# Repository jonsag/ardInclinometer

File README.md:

# ardInclinometer

An inclinometer built around MPU-6050 and ATmega MCUs  

Works on Arduino UNO, not working on barebone MCUs yet.

## Install latest avrdude from git repository

Install prerequisites  
>$ sudo apt install git build-essential cmake libelf-dev libusb-dev libusb-1.0-0-dev libhidapi-dev libftdi-dev libftdi1-dev flex bison  

Download repository  
>$ git clone [https://github.com/avrdudes/avrdude.git](https://github.com/avrdudes/avrdude.git)  

Build  
>$ cd avrdude  
>$ cmake -D CMAKE_BUILD_TYPE=Release -B build_linux  
>$ cmake --build build_linux  

Install (if you have ~/bin in your path)  
>$ cp -r build_linux/src ~/bin/avrdude-bin  
>$ ln -s avrdude-bin/avrdude ~/bin/avrdude  

Check version  
>$ avrdude -?  

    ...
    avrdude version 7.0-20220924 (8f478f0), URL: <https://github.com/avrdudes/avrdude>

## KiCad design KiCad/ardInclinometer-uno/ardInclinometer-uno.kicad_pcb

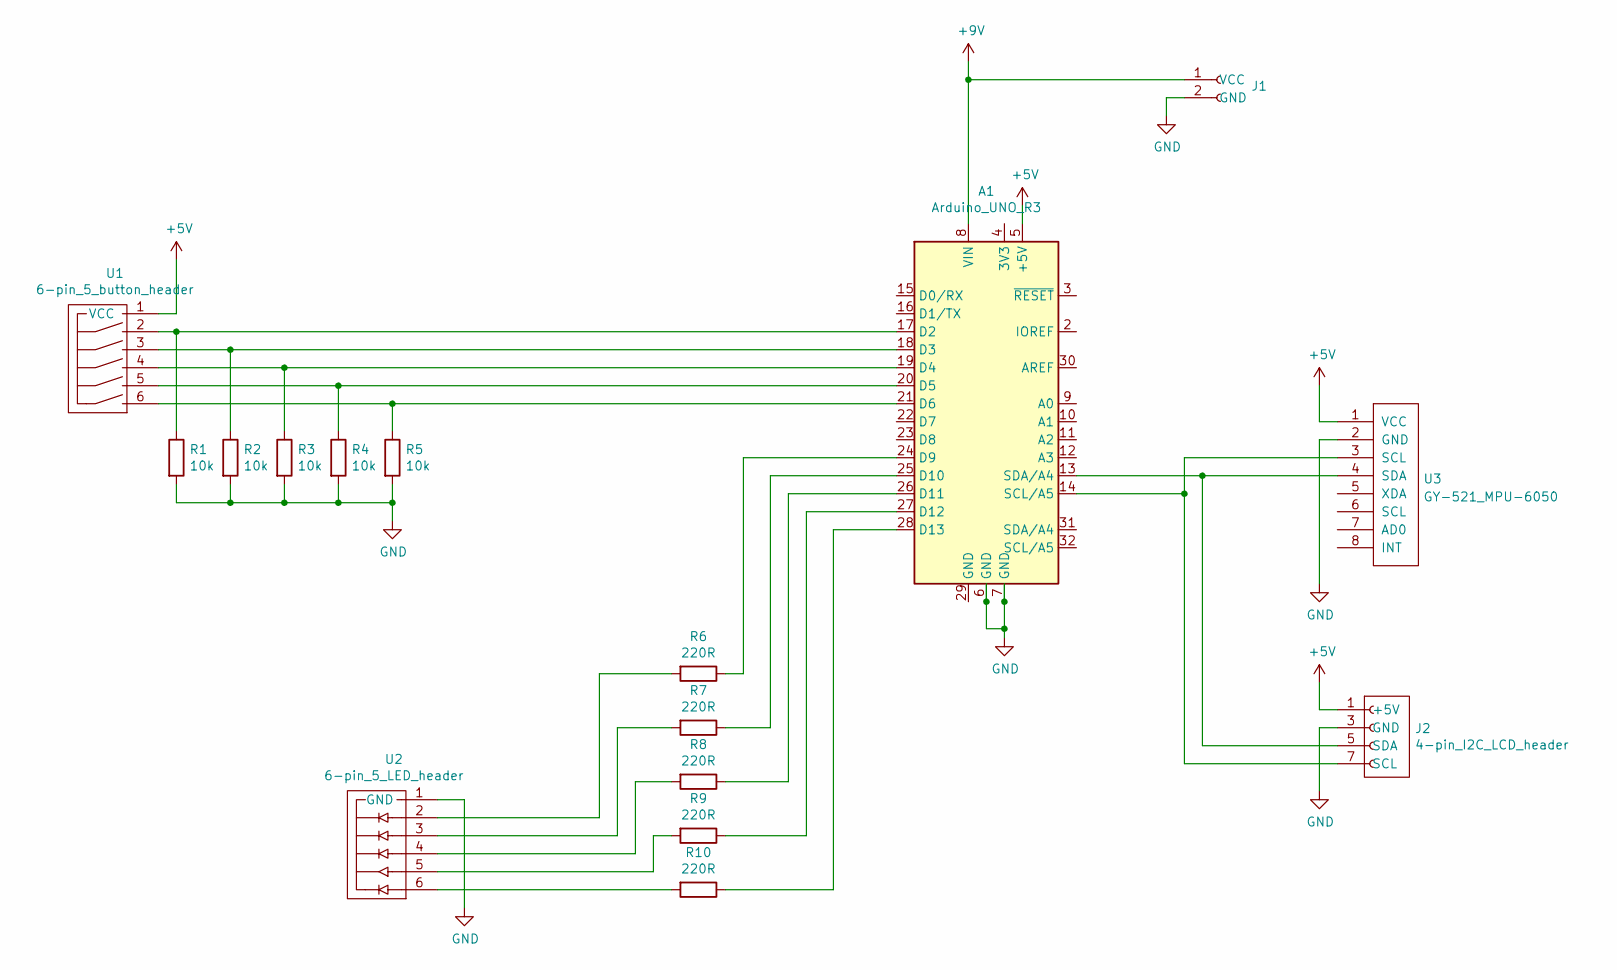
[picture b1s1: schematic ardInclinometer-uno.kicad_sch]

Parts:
A1: Arduino_UNO_R3; Arduino_UNO_R3_shield_large
J1: 2-pin_power_input_header; 2-pin_power_input_header_larger_pads
J2: 4-pin_I2C_LCD_header; 4-pin_I2C_LCD_header_larger
R1, R2, R3, R4, R5: 10k; R_Axial_DIN0207_L6.3mm_D2.5mm_P10.16mm_Horizontal_larger_pa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
R6, R7, R8, R9, R10: 220R; R_Axial_DIN0207_L6.3mm_D2.5mm_P10.16mm_Horizontal_larger_pa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
U1: 6-pin_5_button_header; 6-pin_5_switch_header_large
U2: 6-pin_5_LED_header; 6-pin_5_LED_header_large
U3: GY-521_MPU-6050

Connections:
+5V: A1.5 (+5V), J2.1 (+5V), U1.1 (VCC), U3.1 (VCC)
+9V: A1.8 (VIN), J1.1 (VCC)
GND: A1.6 (GND), A1.7 (GND), J1.2 (GND), J2.3 (GND), R1.2, R2.2, R3.2, R4.2, R5.2, U2.1 (GND), U3.2 (GND)
unnamed: A1.13 (SDA/A4), J2.5 (SDA), U3.4 (SDA)
unnamed: A1.14 (SCL/A5), J2.7 (SCL), U3.3 (SCL)
unnamed: A1.17 (D2), R1.1, U1.2
unnamed: A1.18 (D3), R2.1, U1.3
unnamed: A1.19 (D4), R3.1, U1.4
unnamed: A1.20 (D5), R4.1, U1.5
unnamed: A1.21 (D6), R5.1, U1.6
unnamed: A1.24 (D9), R6.1
unnamed: A1.25 (D10), R7.1
unnamed: A1.26 (D11), R8.1
unnamed: A1.27 (D12), R9.1
unnamed: A1.28 (D13), R10.1
unnamed: R6.2, U2.2
unnamed: R7.2, U2.3
unnamed: R8.2, U2.4
unnamed: R9.2, U2.5
unnamed: R10.2, U2.6

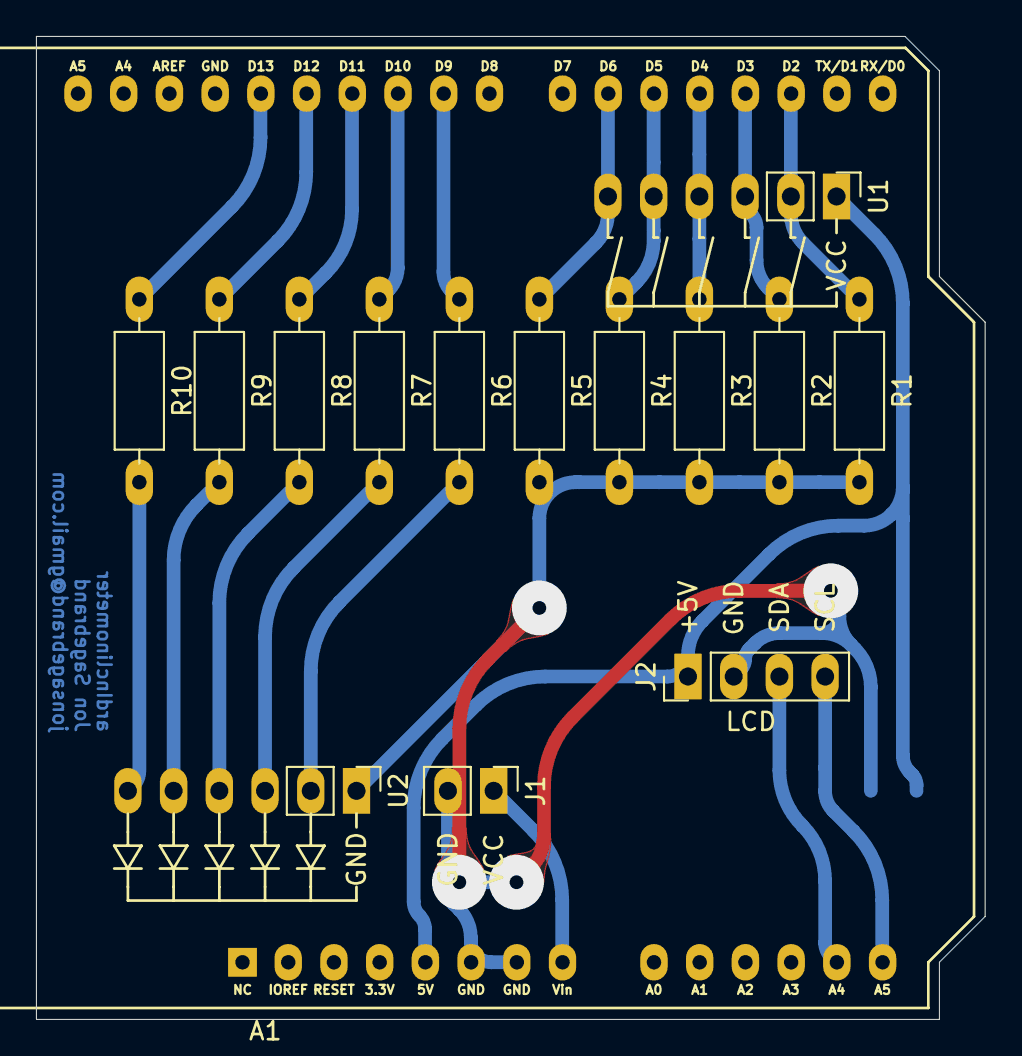
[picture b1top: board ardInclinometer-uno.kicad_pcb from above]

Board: 2 copper layers, 52.7 x 54.6 mm, 15 parts (0 on the bottom side), 20 nets.

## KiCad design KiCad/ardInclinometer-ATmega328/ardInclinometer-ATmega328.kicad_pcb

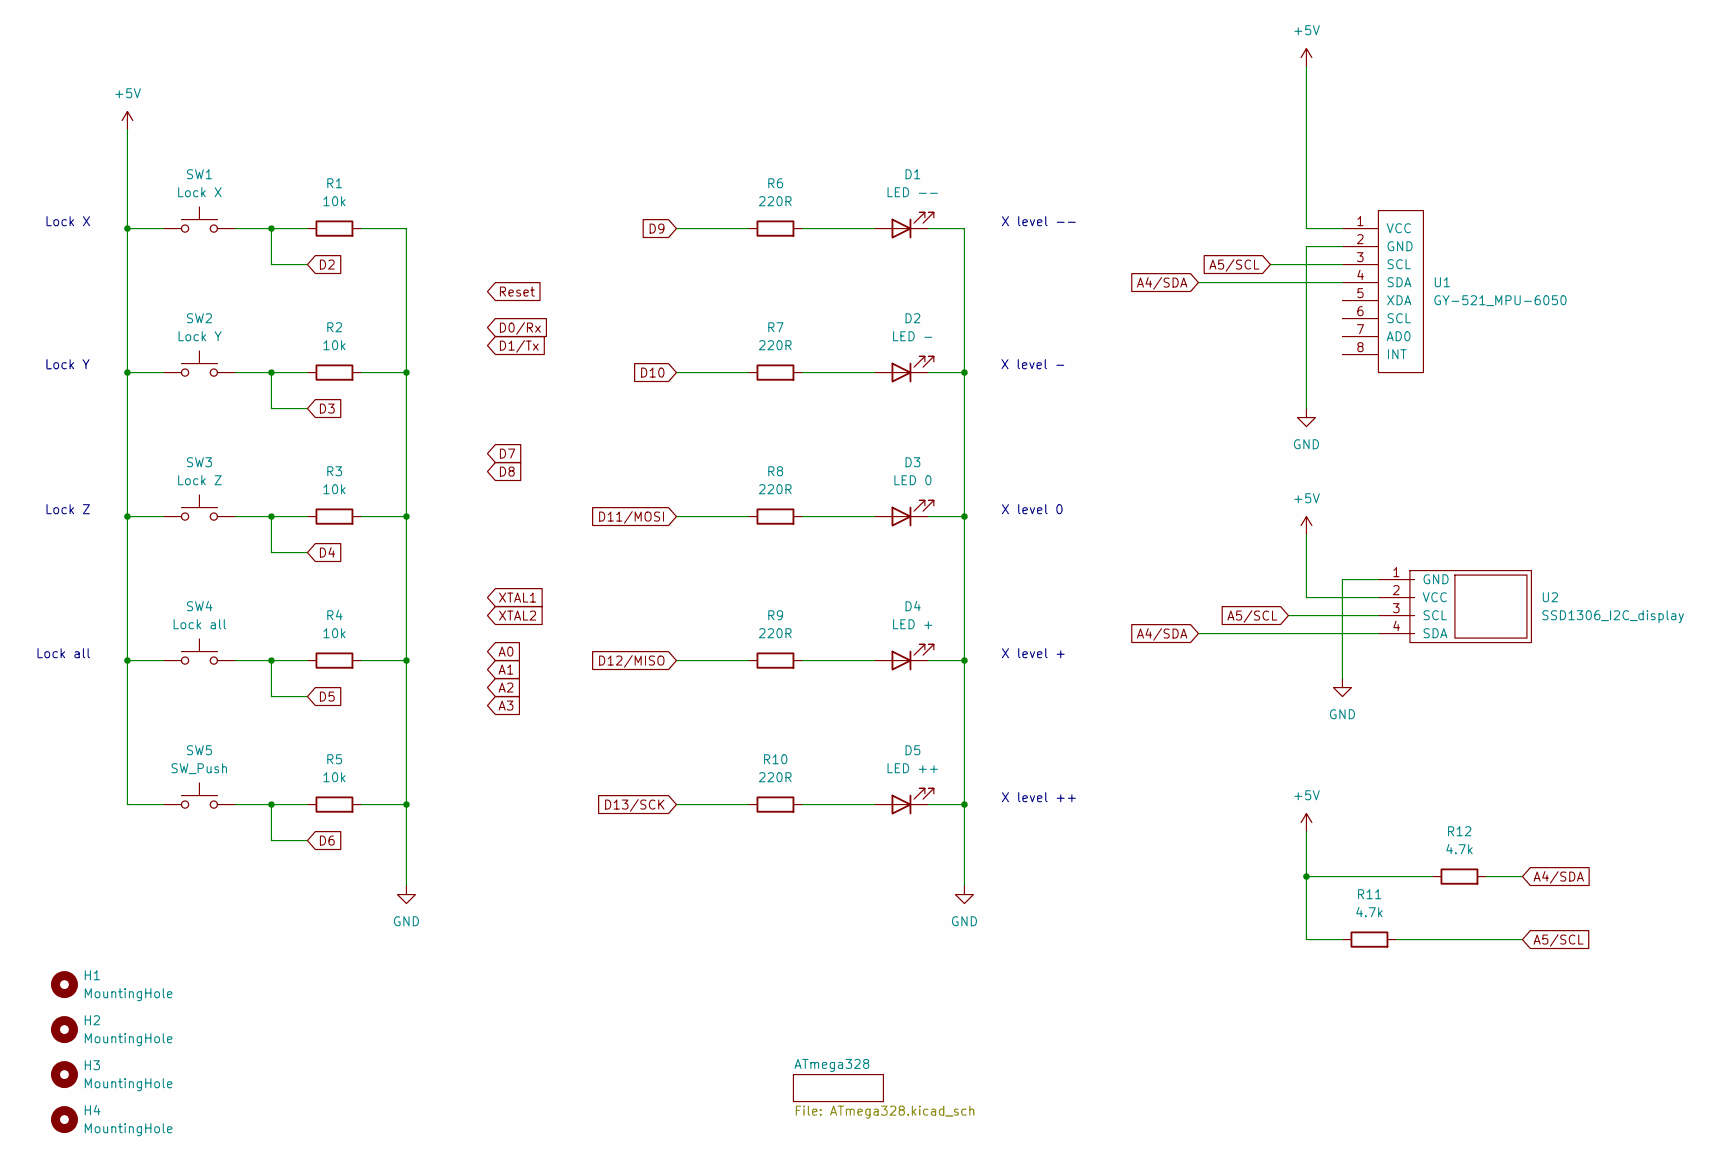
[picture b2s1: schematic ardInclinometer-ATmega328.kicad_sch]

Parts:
D1: LED --; LED_D5.0mm_large
D2: LED -; LED_D5.0mm_large
D3: LED 0; LED_D5.0mm_large
D4: LED +; LED_D5.0mm_large
D5: LED ++; LED_D5.0mm_large
H1, H2, H3, H4: MountingHole; MountingHole_3.2mm_M3
R1, R2, R3, R4, R5: 10k; R_Axial_DIN0207_L6.3mm_D2.5mm_P10.16mm_Horizontal_larger_pa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
R6, R7, R8, R9, R10: 220R; R_Axial_DIN0207_L6.3mm_D2.5mm_P10.16mm_Horizontal_larger_pa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
R11, R12: 4.7k; R_Axial_DIN0207_L6.3mm_D2.5mm_P10.16mm_Horizontal_large
SW1: Lock X; SW_PUSH_6mm_large
SW2: Lock Y; SW_PUSH_6mm_large
SW3: Lock Z; SW_PUSH_6mm_large
SW4: Lock all; SW_PUSH_6mm_large
SW5: SW_Push; SW_PUSH_6mm_large
U1: GY-521_MPU-6050; GY-521_MPU6050_w_header_large
U2: SSD1306_I2C_display; SSD1306_I2C_0.96_OLED_display_large

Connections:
+5V: R11.1, R12.1, SW1.1, SW2.1, SW3.1, SW4.1, SW5.1, U1.1 (VCC), U2.2 (VCC); also elsewhere on the board
A4/SDA: R12.2, U1.4 (SDA), U2.4 (SDA); also elsewhere on the board
A5/SCL: R11.2, U1.3 (SCL), U2.3 (SCL); also elsewhere on the board
D2: R1.1, SW1.2; also elsewhere on the board
D3: R2.1, SW2.2; also elsewhere on the board
D4: R3.1, SW3.2; also elsewhere on the board
D5: R4.1, SW4.2; also elsewhere on the board
D6: R5.1, SW5.2; also elsewhere on the board
D9: R6.1; also elsewhere on the board
D10: R7.1; also elsewhere on the board
D11/MOSI: R8.1; also elsewhere on the board
D12/MISO: R9.1; also elsewhere on the board
D13/SCK: R10.1; also elsewhere on the board
GND: D1.1 (K), D2.1 (K), D3.1 (K), D4.1 (K), D5.1 (K), R1.2, R2.2, R3.2, R4.2, R5.2, U1.2 (GND), U2.1 (GND); also elsewhere on the board
unnamed: D1.2 (A), R6.2
unnamed: D2.2 (A), R7.2
unnamed: D3.2 (A), R8.2
unnamed: D4.2 (A), R9.2
unnamed: D5.2 (A), R10.2

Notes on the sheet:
X level +
Lock all
Lock Z
X level -
X level ++
Lock X
Lock Y
X level --
X level 0

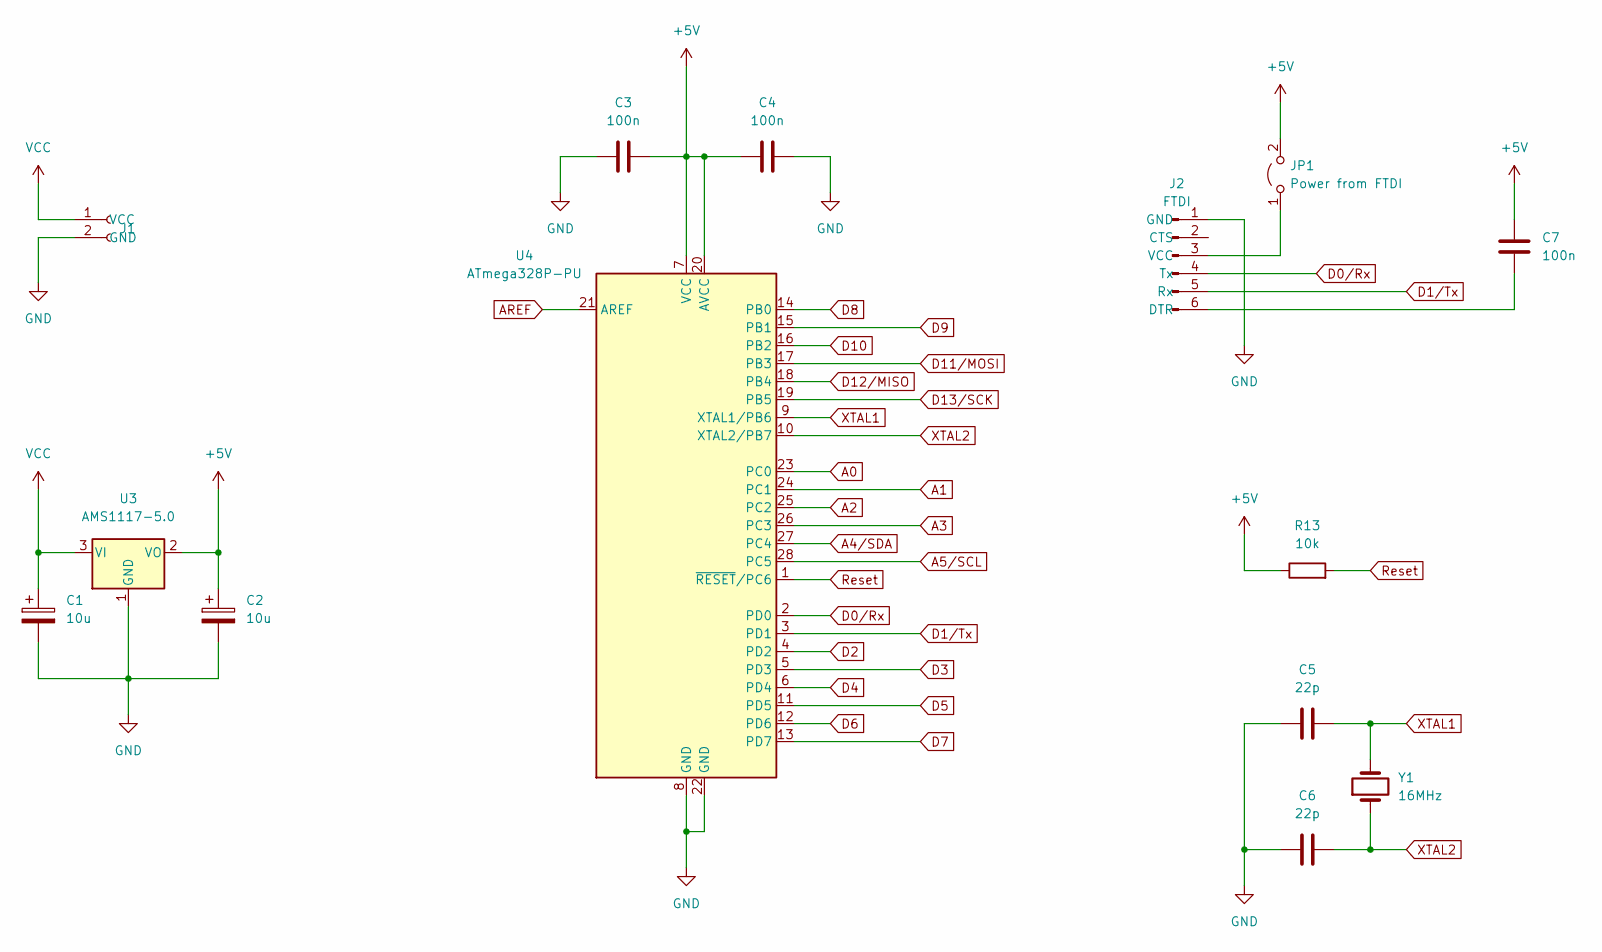
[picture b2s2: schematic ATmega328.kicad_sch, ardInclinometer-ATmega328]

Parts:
C1, C2: 10u; CP_Radial_D5.0mm_P2.00mm_larger
C3, C4, C7: 100n; C_Disc_D4.3mm_W1.9mm_P5.00mm_large
C5, C6: 22p; C_Disc_D3.0mm_W1.6mm_P2.50mm_larg
J1: Power in; 2-pin_power_input_header_larger_pads
J2: FTDI; 6-pin FTDI Programmer PinSocket large
JP1: Power from FTDI; Jumper_1x02_P2.54mm_large
R13: 10k; R_Axial_DIN0207_L6.3mm_D2.5mm_P10.16mm_Horizontal_larger_pa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
U3: AMS1117-5.0; SOT-223-3_TabPin2
U4: ATmega328P-PU; DIP-28_W7.62mm_LongPads w socket
Y1: 16MHz; Crystal_HC49-4H_Vertical_large

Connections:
+5V: C2.1, C3.1, C4.2, C7.2, JP1.2 (B), R13.1, U3.2 (VO), U4.7 (VCC), U4.20 (AVCC); also elsewhere on the board
A0: U4.23 (PC0)
A1: U4.24 (PC1)
A2: U4.25 (PC2)
A3: U4.26 (PC3)
A4/SDA: U4.27 (PC4); also elsewhere on the board
A5/SCL: U4.28 (PC5); also elsewhere on the board
AREF: U4.21 (AREF)
D0/Rx: J2.4 (Tx), U4.2 (PD0)
D1/Tx: J2.5 (Rx), U4.3 (PD1)
D2: U4.4 (PD2); also elsewhere on the board
D3: U4.5 (PD3); also elsewhere on the board
D4: U4.6 (PD4); also elsewhere on the board
D5: U4.11 (PD5); also elsewhere on the board
D6: U4.12 (PD6); also elsewhere on the board
D7: U4.13 (PD7)
D8: U4.14 (PB0)
D9: U4.15 (PB1); also elsewhere on the board
D10: U4.16 (PB2); also elsewhere on the board
D11/MOSI: U4.17 (PB3); also elsewhere on the board
D12/MISO: U4.18 (PB4); also elsewhere on the board
D13/SCK: U4.19 (PB5); also elsewhere on the board
GND: C1.2, C2.2, C3.2, C4.1, C5.1, C6.1, J1.2 (GND), J2.1 (GND), U3.1 (GND), U4.8 (GND), U4.22 (GND); also elsewhere on the board
unnamed: C7.1, J2.6 (DTR)
unnamed: J2.3 (VCC), JP1.1 (A)
Reset: R13.2, U4.1 (~RESET/PC6)
VCC: C1.1, J1.1 (VCC), U3.3 (VI)
XTAL1: C5.2, U4.9 (XTAL1/PB6), Y1.2
XTAL2: C6.2, U4.10 (XTAL2/PB7), Y1.1

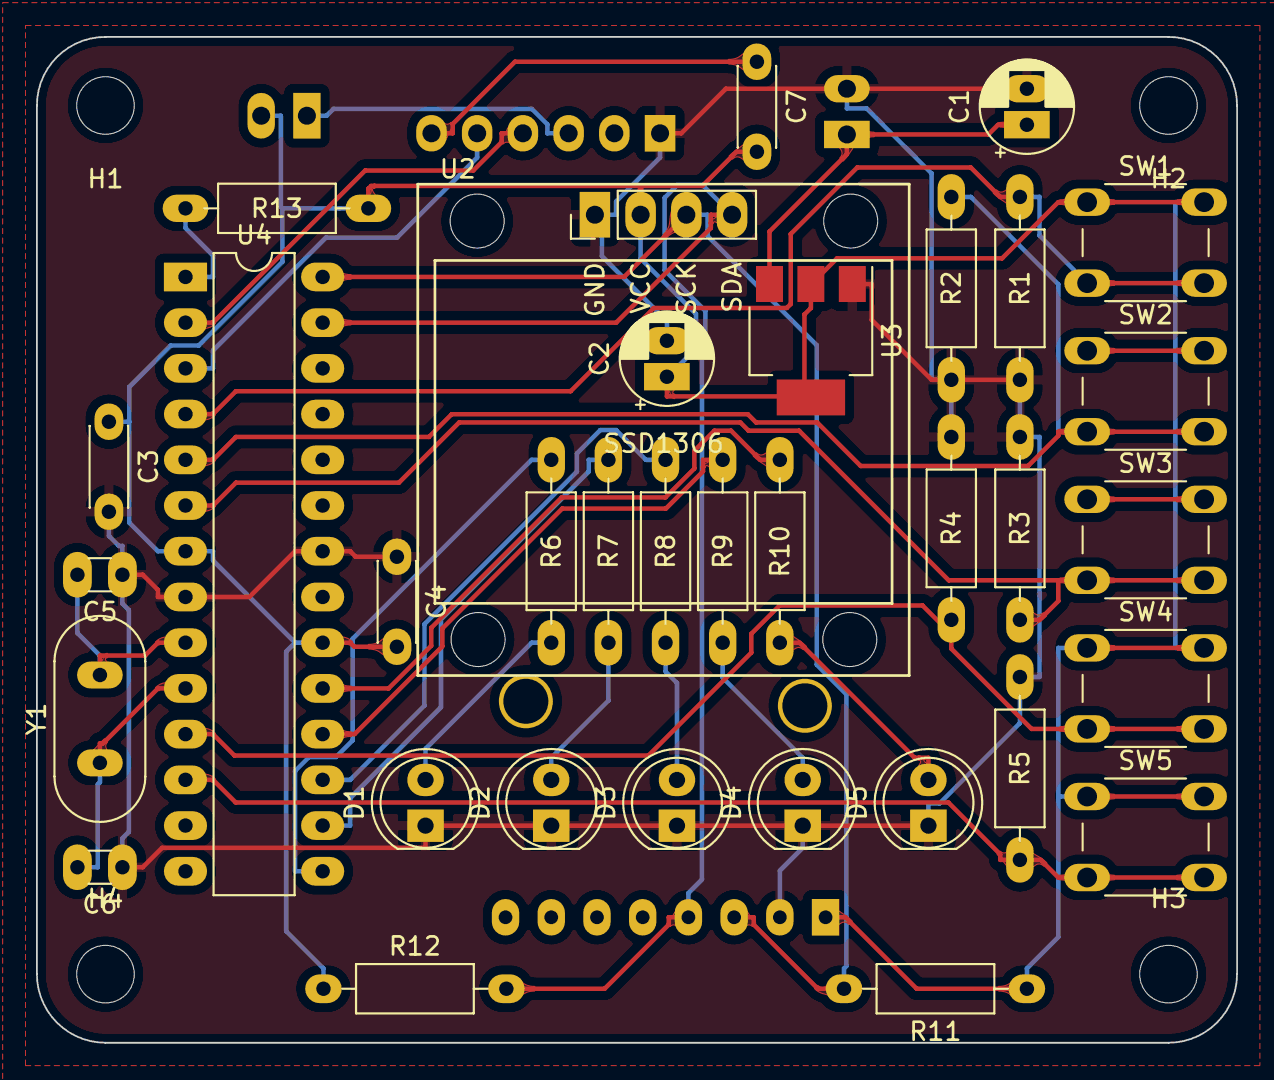
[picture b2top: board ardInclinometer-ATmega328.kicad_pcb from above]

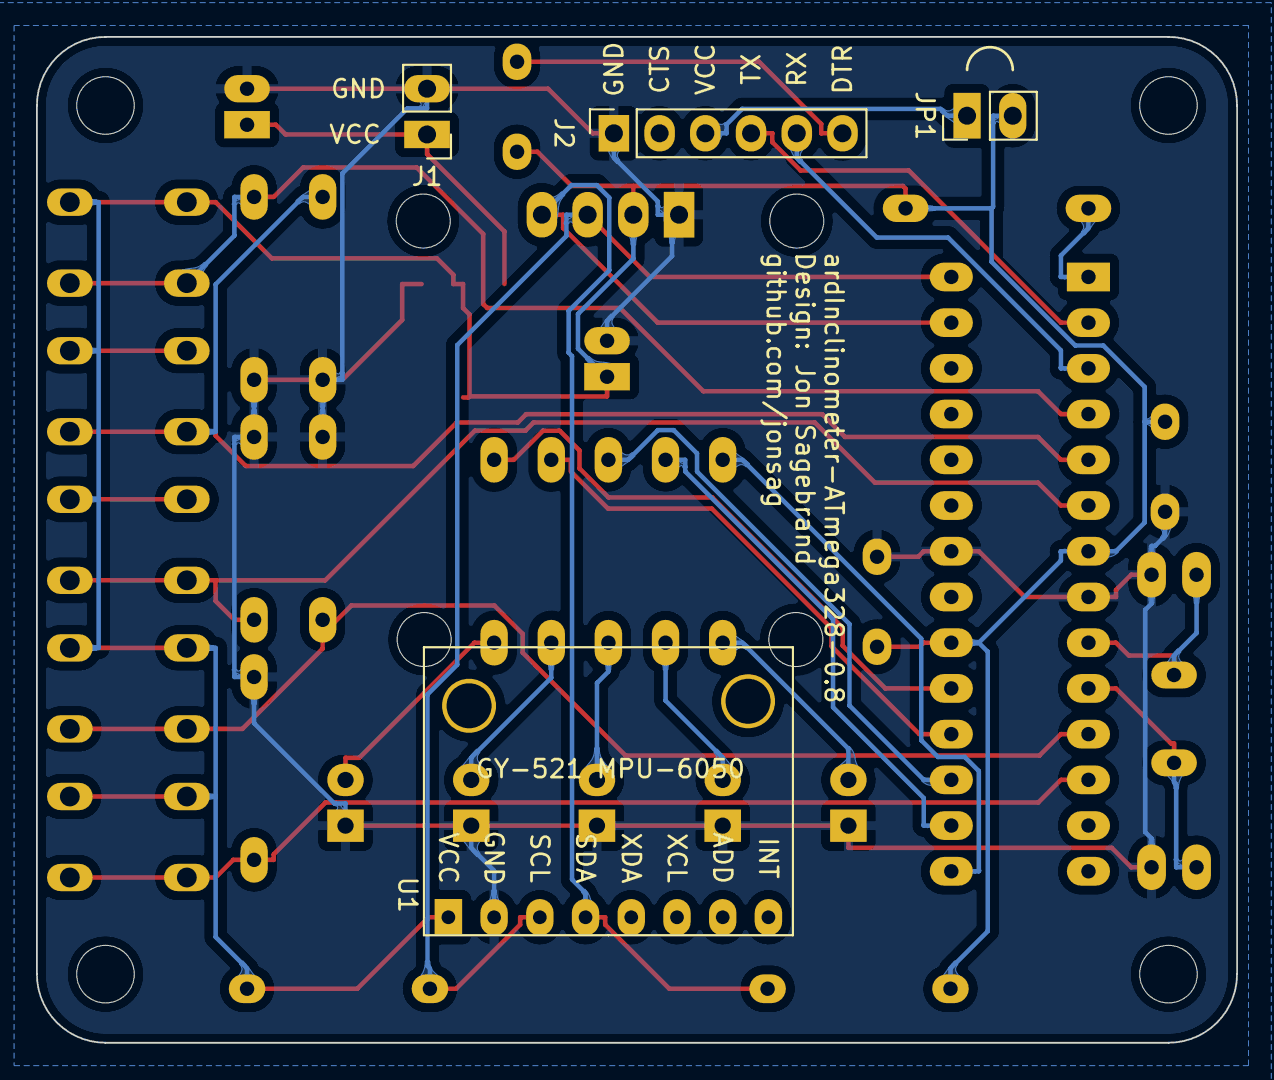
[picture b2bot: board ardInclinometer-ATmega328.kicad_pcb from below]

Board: 2 copper layers, 66.7 x 55.9 mm, 42 parts (4 on the bottom side), 27 nets.

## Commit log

2020-03-14 added KiCad
2020-03-14 added initial sketch from https://dronebotworkshop.com/mpu-6050-level/
2020-06-13 first sketch, lights LEDs
2020-06-13 sketch now prints angles to LCD
2020-06-14 prints to OLED, locks angles
2020-06-15 prints messages
2020-06-16 started on a casing
2020-06-16 casing has lid
2020-06-16 prints text in lid recess
2020-06-16 added gy-521 module
2020-06-17 added screen wedge
2020-06-17 added screen cut out
2020-06-17 started with screen mount
2020-06-17 screen posts
2020-06-18 moved screen posts
2020-06-18 started on OLED screen
2020-06-18 added header comment
2020-06-19 added button holes
2020-06-20 added mount for mpu
2020-06-20 schematics and casing
2020-06-27 uno casing and schematics
2021-01-02 added scads
2021-01-02 removes
2022-09-09 atmega328 kicad
2022-09-09 kicad
2022-09-25 atmega casing
2022-09-25 deletions
2022-09-25 casing looks good for now
2022-09-27 casing finished
2022-09-28 scad
2022-09-28 readme
2022-09-28 new pio environment
2022-09-28 misspelled
2022-09-28 moved
2022-10-01 pio ini
2022-10-02 better enclosure
2022-10-02 better length of lid posts
2022-10-04 more text on box
2022-10-08 working out kinks
2022-10-08 new schematics and pcb
2022-10-08 renames
2022-10-08 more mistakes corrected...
2022-10-09 kicad corrections and dev
2022-10-09 works on code
2022-10-21 kicad v0.6
2022-12-02 added stl of board
2023-02-21 kicad7
